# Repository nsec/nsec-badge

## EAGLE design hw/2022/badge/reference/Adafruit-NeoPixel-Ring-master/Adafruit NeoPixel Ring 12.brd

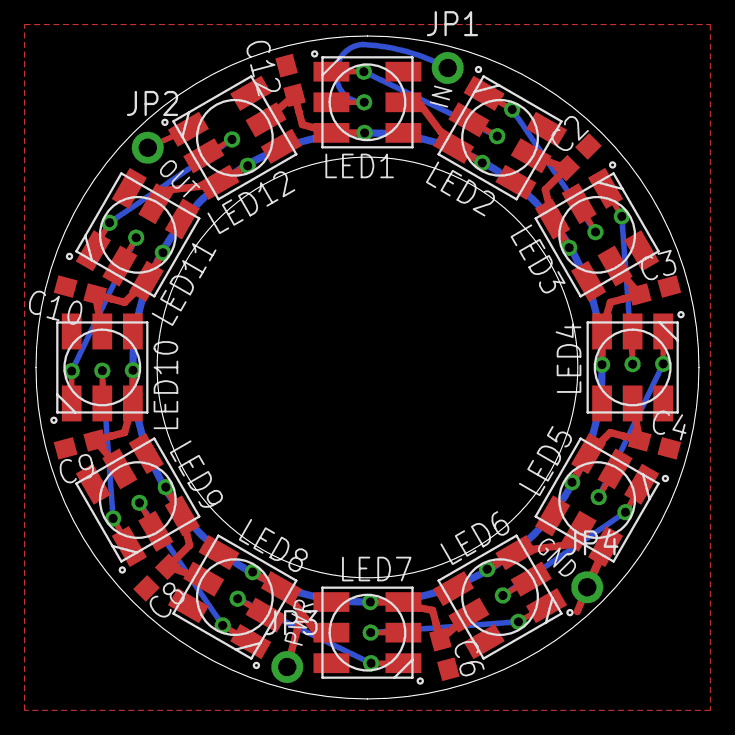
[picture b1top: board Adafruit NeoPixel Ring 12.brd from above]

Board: 2 copper layers, 36.8 x 36.8 mm, 27 parts (1 on the bottom side), 15 nets.

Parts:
C2, C3, C4, C6, C8, C9, C10, C12: C0603
JP1, JP2, JP3, JP4: 1X01-CLEANBIG
LED1, LED2, LED3, LED4, LED5, LED6, LED7, LED8, LED9, LED10, LED11, LED12: WS28115050
U$1, U$2: GUIDE-STAR-12
U$3: ADAFRUIT_5MM

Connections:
GND: C2.2, C3.2, C4.2, C6.2, C8.2, C9.2, C10.2, C12.2, JP4.1, LED1.VSS, LED2.VSS, LED3.VSS, LED4.VSS, LED5.VSS, LED6.VSS, LED7.VSS, LED8.VSS, LED9.VSS, LED10.VSS, LED11.VSS, LED12.VSS
unnamed: LED1.DO, LED2.DI
unnamed: LED2.DO, LED3.DI
unnamed: LED3.DO, LED4.DI
unnamed: LED4.DO, LED5.DI
unnamed: LED5.DO, LED6.DI
unnamed: LED6.DO, LED7.DI
unnamed: LED7.DO, LED8.DI
unnamed: LED8.DO, LED9.DI
unnamed: LED9.DO, LED10.DI
unnamed: LED10.DO, LED11.DI
unnamed: LED11.DO, LED12.DI
unnamed: JP1.1, LED1.DI
unnamed: JP2.1, LED12.DO
VDD: C2.1, C3.1, C4.1, C6.1, C8.1, C9.1, C10.1, C12.1, JP3.1, LED1.LEDVDD, LED1.VDD, LED2.LEDVDD, LED2.VDD, LED3.LEDVDD, LED3.VDD, LED4.LEDVDD, LED4.VDD, LED5.LEDVDD, LED5.VDD, LED6.LEDVDD, LED6.VDD, LED7.LEDVDD, LED7.VDD, LED8.LEDVDD, LED8.VDD, LED9.LEDVDD, LED9.VDD, LED10.LEDVDD, LED10.VDD, LED11.LEDVDD, LED11.VDD, LED12.LEDVDD, LED12.VDD

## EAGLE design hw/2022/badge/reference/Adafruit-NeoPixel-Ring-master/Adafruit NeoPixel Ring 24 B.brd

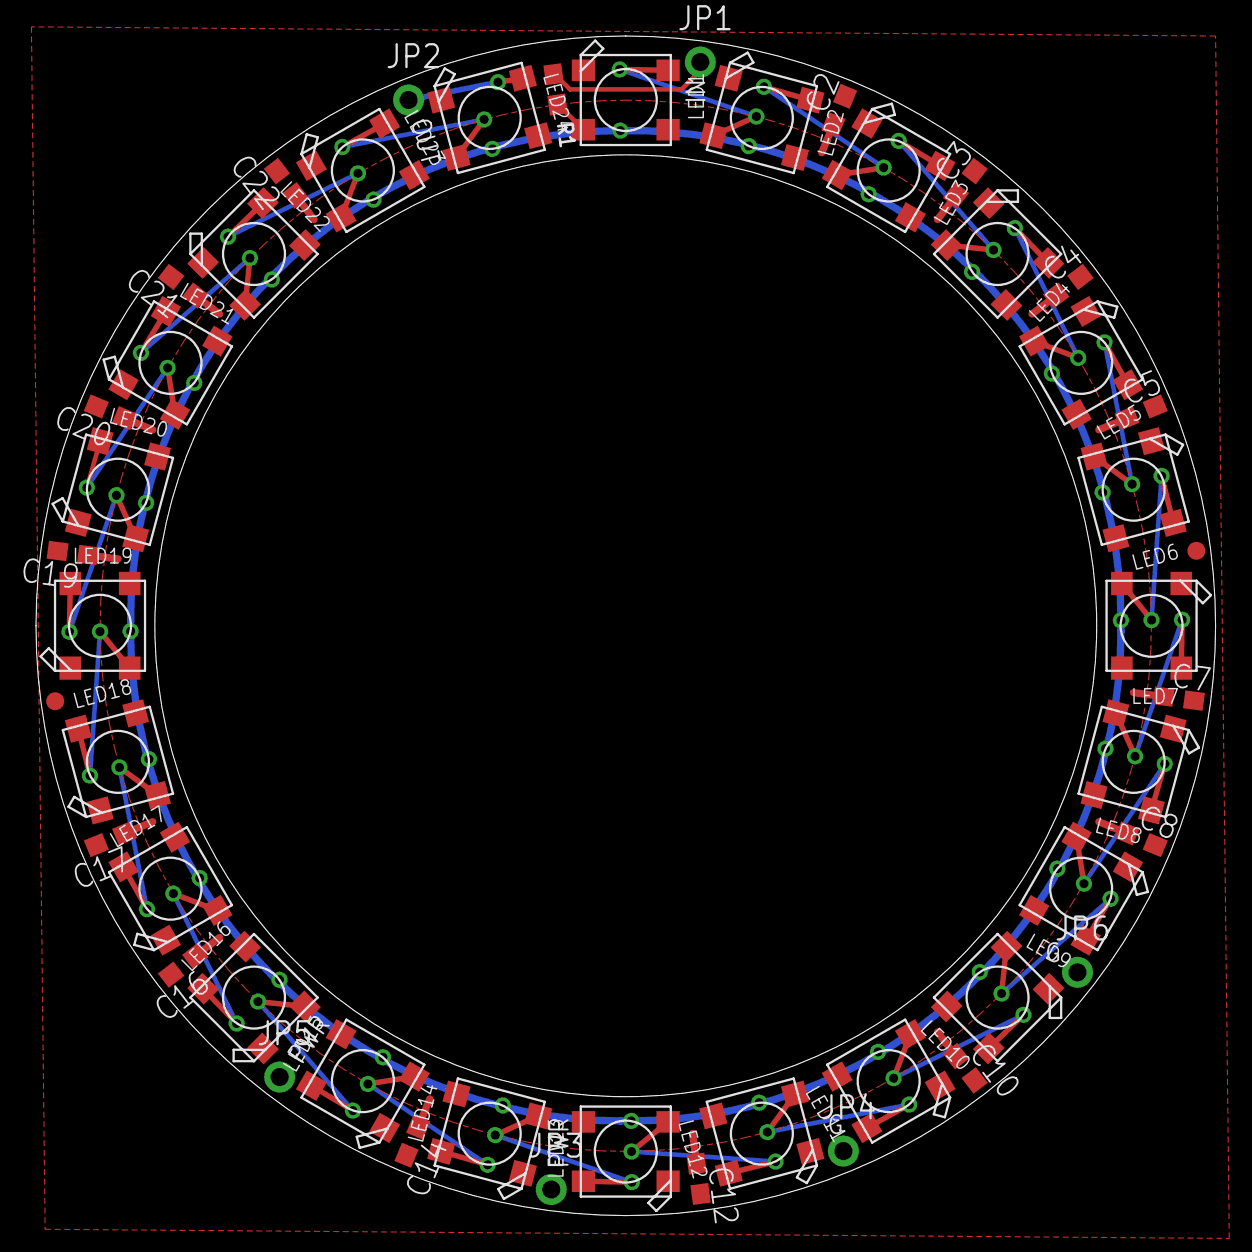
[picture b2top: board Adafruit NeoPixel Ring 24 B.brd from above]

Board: 2 copper layers, 65.5 x 65.5 mm, 49 parts (1 on the bottom side), 28 nets.

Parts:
C2, C3, C4, C5, C7, C8, C10, C12, C14, C16, C17, C19, C20, C21, C22: C0603
FID1, FID2: FIDUCIAL""; FIDUCIAL_1MM
JP1, JP2, JP3, JP4, JP5, JP6: 1X01-CLEANBIG
LED1, LED2, LED3, LED4, LED5, LED6, LED7, LED8, LED9, LED10, LED11, LED12, LED13, LED14, LED15, LED16, LED17, LED18, LED19, LED20, LED21, LED22, LED23, LED24: WS2812B5050; WS2812B-NARROW
R1: 0603-NO
U$1: ADAFRUIT_5MM

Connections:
GND: C2.2, C3.2, C4.2, C5.2, C7.2, C8.2, C10.2, C12.2, C14.2, C16.2, C17.2, C19.2, C20.2, C21.2, C22.2, JP4.1, JP6.1, LED1.3-GND, LED2.3-GND, LED3.3-GND, LED4.3-GND, LED5.3-GND, LED6.3-GND, LED7.3-GND, LED8.3-GND, LED9.3-GND, LED10.3-GND, LED11.3-GND, LED12.3-GND, LED13.3-GND, LED14.3-GND, LED15.3-GND, LED16.3-GND, LED17.3-GND, LED18.3-GND, LED19.3-GND, LED20.3-GND, LED21.3-GND, LED22.3-GND, LED23.3-GND, LED24.3-GND
unnamed: LED1.2-DOUT, LED2.4-DIN
unnamed: LED2.2-DOUT, LED3.4-DIN
unnamed: LED3.2-DOUT, LED4.4-DIN
unnamed: LED4.2-DOUT, LED5.4-DIN
unnamed: LED5.2-DOUT, LED6.4-DIN
unnamed: LED6.2-DOUT, LED7.4-DIN
unnamed: LED7.2-DOUT, LED8.4-DIN
unnamed: LED8.2-DOUT, LED9.4-DIN
unnamed: LED9.2-DOUT, LED10.4-DIN
unnamed: LED10.2-DOUT, LED11.4-DIN
unnamed: LED11.2-DOUT, LED12.4-DIN
unnamed: LED12.2-DOUT, LED13.4-DIN
unnamed: LED13.2-DOUT, LED14.4-DIN
unnamed: LED14.2-DOUT, LED15.4-DIN
unnamed: LED15.2-DOUT, LED16.4-DIN
unnamed: LED16.2-DOUT, LED17.4-DIN
unnamed: LED17.2-DOUT, LED18.4-DIN
unnamed: LED18.2-DOUT, LED19.4-DIN
unnamed: LED19.2-DOUT, LED20.4-DIN
unnamed: LED20.2-DOUT, LED21.4-DIN
unnamed: LED21.2-DOUT, LED22.4-DIN
unnamed: LED22.2-DOUT, LED23.4-DIN
unnamed: LED23.2-DOUT, LED24.4-DIN
unnamed: JP2.1, LED24.2-DOUT
unnamed: LED1.4-DIN, R1.2
unnamed: JP1.1, R1.1
VDD: C2.1, C3.1, C4.1, C5.1, C7.1, C8.1, C10.1, C12.1, C14.1, C16.1, C17.1, C19.1, C20.1, C21.1, C22.1, JP3.1, JP5.1, LED1.1-VDD, LED2.1-VDD, LED3.1-VDD, LED4.1-VDD, LED5.1-VDD, LED6.1-VDD, LED7.1-VDD, LED8.1-VDD, LED9.1-VDD, LED10.1-VDD, LED11.1-VDD, LED12.1-VDD, LED13.1-VDD, LED14.1-VDD, LED15.1-VDD, LED16.1-VDD, LED17.1-VDD, LED18.1-VDD, LED19.1-VDD, LED20.1-VDD, LED21.1-VDD, LED22.1-VDD, LED23.1-VDD, LED24.1-VDD

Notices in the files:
parts and their libraries:
microbuilder: This work is placed in the public domain, and may be freely used for commercial and non-commercial work with the following conditions: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
